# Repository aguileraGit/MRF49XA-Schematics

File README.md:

MRF49XA-Schematics
==================

MRF49XA Schematics and Layout

Project page for a wireless board. This board uses the MicroChip MRF49XA and Atmel ATMEGA32U4.

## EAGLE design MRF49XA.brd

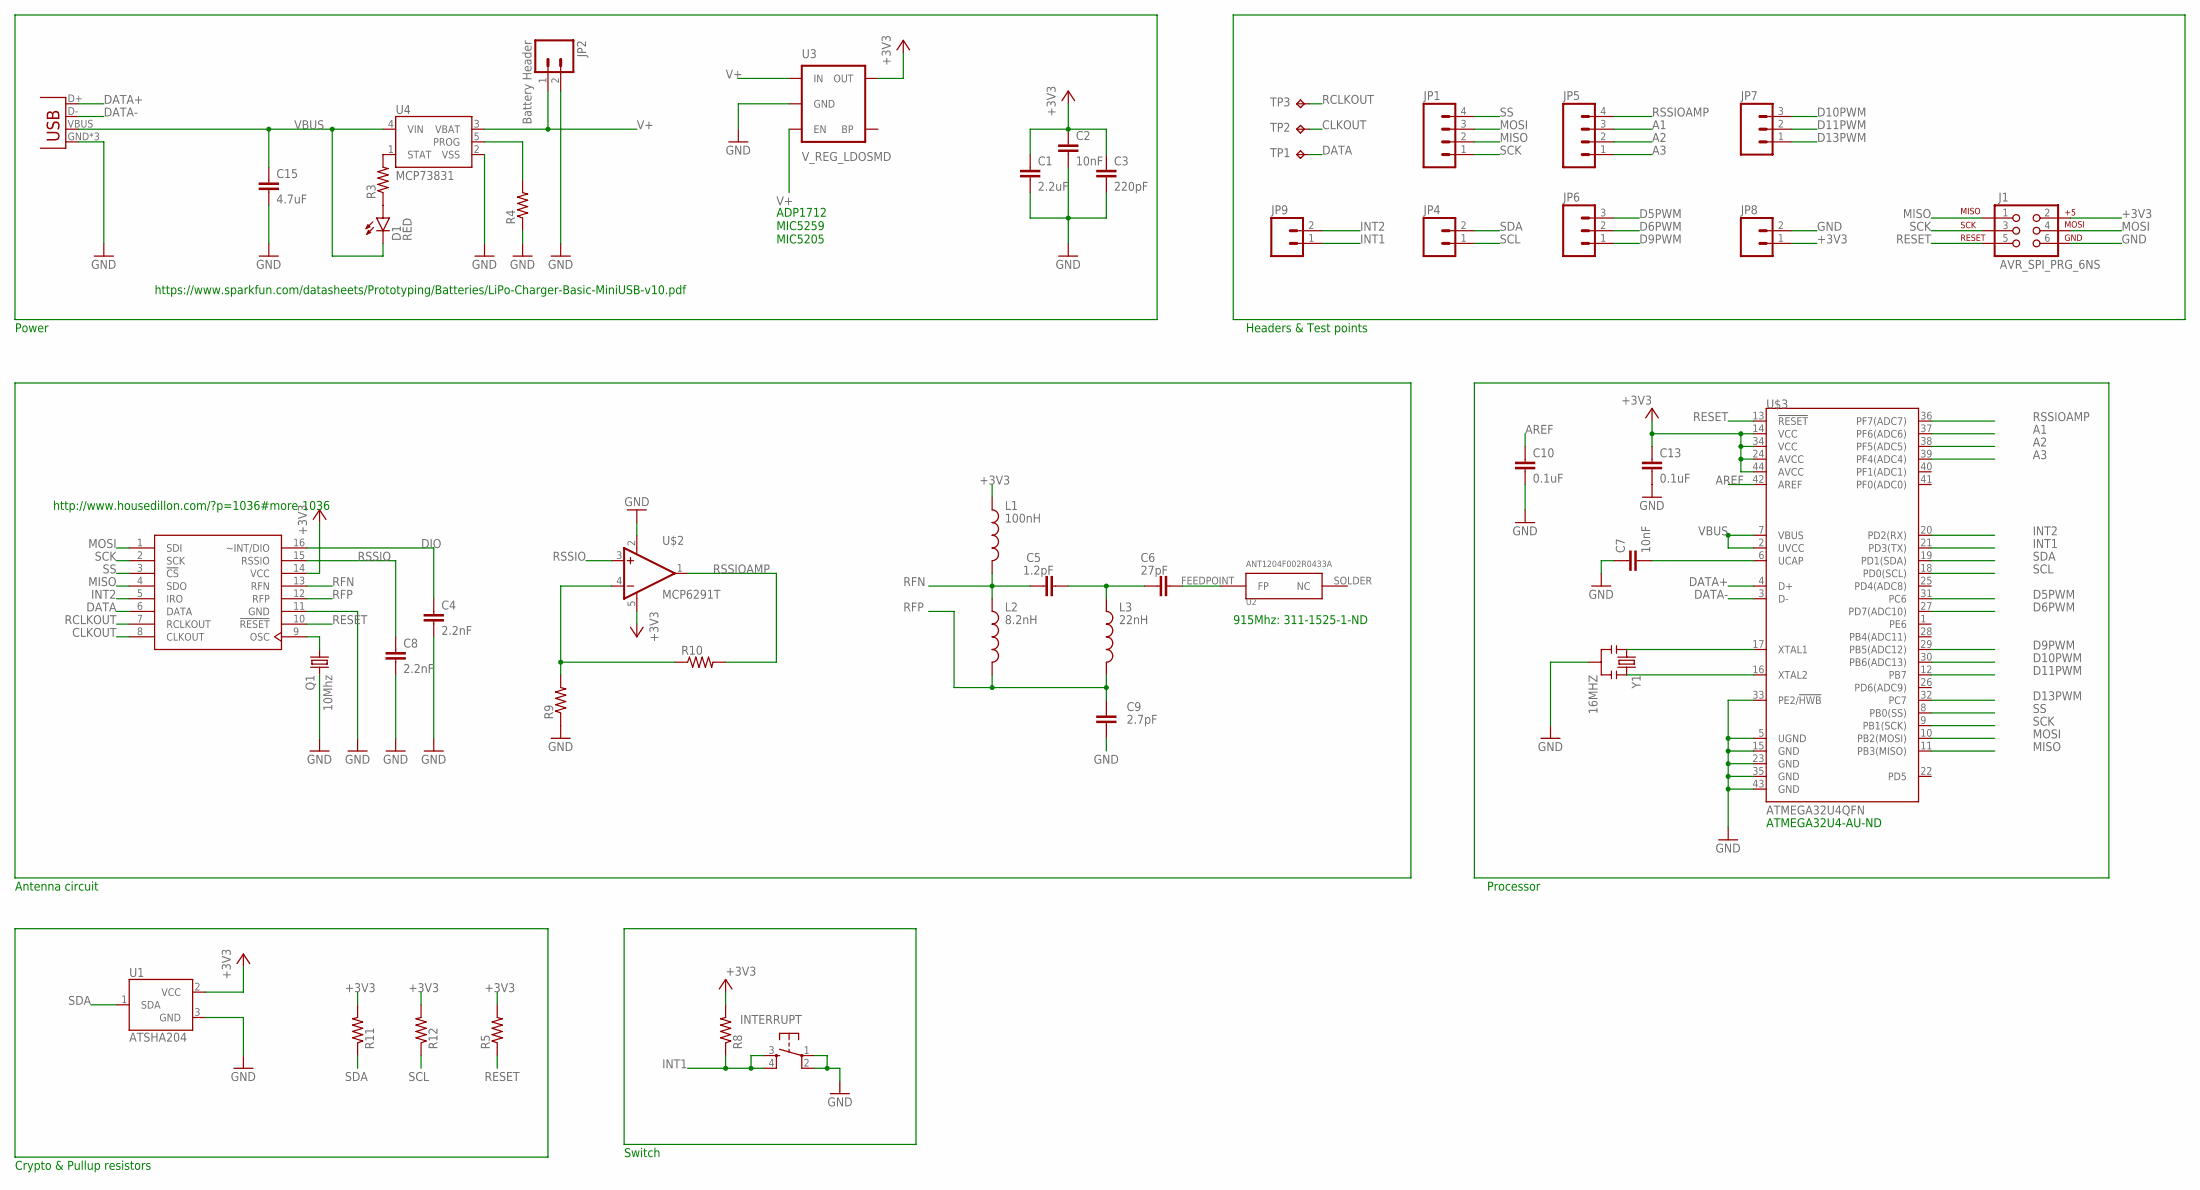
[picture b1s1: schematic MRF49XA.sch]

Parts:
C1: 2.2uF; 0603-CAP
C2, C7: 10nF; 0603-CAP
C3: 220pF; 0603-CAP
C4, C8: 2.2nF; 0603-CAP
C5: 1.2pF; 0603-CAP
C6: 27pF; 0603-CAP
C9: 2.7pF; 0603-CAP
C10, C13: 0.1uF; 0603-CAP
C15: 4.7uF; C3216
D1: RED; LED-0603
INTERRUPT: TAC_SWITCHSMD; TACTILE-SWITCH-SMD
J1: AVR_SPI_PRG_6NS; 2X3-NS
JP1, JP5: M04PTH; 1X04
JP2: Battery Header; 1X02_LOCK_LONGPADS
JP3: USB-MICROB
JP4, JP8, JP9: M02PTH; 1X02
JP6, JP7: M03PTH; 1X03
L1: 100nH; 0603
L2: 8.2nH; 0603
L3: 22nH; 0603
Q1: 10Mhz; CTS406
R3: RESISTOR0603-RES; 0603-RES
R4, R5, R8, R9, R10, R11, R12: R-US_R0603; R0603
TP1, TP2, TP3: TPTP08R; TP08R
U1: ATSHA204; SOT23-3
U2: ANT1204F002R0433A
U3: V_REG_LDOSMD; SOT23-5
U4: MCP73831; SOT23-5
U$1: MRF49XA; TSSOP16
U$2: MCP6291T; SOT23-5
U$3: ATMEGA32U4QFN; QFN-44
Y1: 16MHZ; RESONATOR-SMD

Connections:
+3V3: C1.1, C2.1, C3.1, C13.1, J1.2, JP8.1, L1.1, R5.2, R8.2, R11.2, R12.2, U1.2 (VCC), U3.5 (OUT), U$1.14 (VCC), U$2.5 (V+), U$3.14 (VCC), U$3.24 (AVCC), U$3.34 (VCC), U$3.44 (AVCC)
A1: JP5.3, U$3.37 (PF6(ADC6))
A2: JP5.2, U$3.38 (PF5(ADC5))
A3: JP5.1, U$3.39 (PF4(ADC4))
AREF: C10.1, U$3.42 (AREF)
CLKOUT: TP2.TP, U$1.8 (CLKOUT)
D5PWM: JP6.3, U$3.31 (PC6)
D6PWM: JP6.2, U$3.27 (PD7(ADC10))
D9PWM: JP6.1, U$3.29 (PB5(ADC12))
D10PWM: JP7.3, U$3.30 (PB6(ADC13))
D11PWM: JP7.2, U$3.12 (PB7)
D13PWM: JP7.1, U$3.32 (PC7)
DATA: TP1.TP, U$1.6 (DATA)
DATA+: JP3.D+, U$3.4 (D+)
DATA-: JP3.D-, U$3.3 (D-)
DIO: C4.1, U$1.16 (~INT/DIO)
GND: C1.2, C2.2, C3.2, C4.2, C7.1, C8.2, C9.2, C10.2, C13.2, C15.2, INTERRUPT.1, INTERRUPT.2, J1.6, JP2.2, JP3.GND, JP3.MT1 (GND), JP3.MT2 (GND), JP8.2, Q1.3 (2), R4.1, R9.1, U1.3 (GND), U3.2 (GND), U4.2 (VSS), U$1.11 (GND), U$2.2 (V-), U$3.5 (UGND), U$3.15 (GND), U$3.23 (GND), U$3.33 (PE2/!HWB), U$3.35 (GND), U$3.43 (GND), Y1.2
INT1: INTERRUPT.3, INTERRUPT.4, JP9.1, R8.1, U$3.21 (PD3(TX))
INT2: JP9.2, U$1.5 (IRO), U$3.20 (PD2(RX))
MISO: J1.1, JP1.2, U$1.4 (SDO), U$3.11 (PB3(MISO))
MOSI: J1.4, JP1.3, U$1.1 (SDI), U$3.10 (PB2(MOSI))
unnamed: Q1.1, U$1.9 (OSC)
unnamed: U$3.16 (XTAL2), Y1.3
unnamed: U$3.17 (XTAL1), Y1.1
unnamed: R3.2, U4.1 (STAT)
unnamed: D1.A, R3.1
unnamed: R4.2, U4.5 (PROG)
unnamed: C7.2, U$3.6 (UCAP)
unnamed: C5.2, C6.1, L3.1
unnamed: R9.2, R10.1, U$2.4 (-IN)
unnamed: C6.2, U2.FEEDPOINT (FP)
RCLKOUT: TP3.TP, U$1.7 (RCLKOUT)
RESET: J1.5, R5.1, U$1.10 (!RESET), U$3.13 (!RESET)
RFN: C5.1, L1.2, L2.1, U$1.13 (RFN)
RFP: C9.1, L2.2, L3.2, U$1.12 (RFP)
RSSIO: C8.1, U$1.15 (RSSIO), U$2.3 (+IN)
RSSIOAMP: JP5.4, R10.2, U$2.1 (OUT), U$3.36 (PF7(ADC7))
SCK: J1.3, JP1.1, U$1.2 (SCK), U$3.9 (PB1(SCK))
SCL: JP4.1, R12.1, U$3.18 (PD0(SCL))
SDA: JP4.2, R11.1, U1.1 (SDA), U$3.19 (PD1(SDA))
SS: JP1.4, U$1.3 (!CS), U$3.8 (PB0(SS))
V+: JP2.1, U3.1 (IN), U3.3 (EN), U4.3 (VBAT)
VBUS: C15.1, D1.C, JP3.VBUS, U4.4 (VIN), U$3.2 (UVCC), U$3.7 (VBUS)
VSS: U$1.P$1 (VSS)

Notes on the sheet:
https://www.sparkfun.com/datasheets/Prototyping/Batteries/LiPo-Charger-Basic-MiniUSB-v10.pdf
http://www.housedillon.com/?p=1036#more-1036
ATMEGA32U4-AU-ND
915Mhz: 311-1525-1-ND
Power
Antenna circuit
Crypto & Pullup resistors
Switch
Processor
Headers & Test points
ADP1712 MIC5259 MIC5205

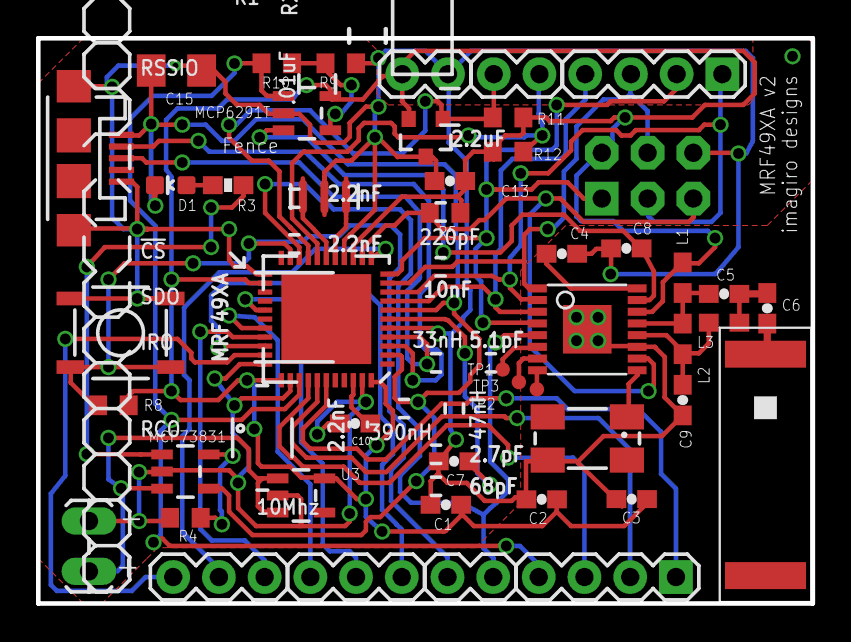
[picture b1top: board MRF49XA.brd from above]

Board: 2 copper layers, 43.0 x 31.4 mm, 47 parts (0 on the bottom side), 43 nets.

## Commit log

2014-12-09 MRF49XA Schematics
    Contains schematics and layout.
2014-12-11 PDF
    Added PDF of the circuit.
2014-12-12 Linear regulator changed
    Changed it. Cheaper. Plus the other one would have blown up my circuit.
2014-12-16 Capacitor and V reg
    Added Aref capacitor. Changed voltage regulator.
2014-12-18 Updates & PDF
    More updates and PDF
2014-12-19 V Regulators
    Added a list of possible voltage regulators.
2014-12-31 BOM
    Added BOM and values to antenna section
2014-12-31 Created README.md
2015-01-09 Adding bootloader
2015-01-13 Code
    Adding code
2015-01-13 Code update
2015-01-14 CS
    Updated the CS pin.
    Adding SPI debug file
2015-01-14 Code update
    Added sendPacket
2015-01-15 Code update
    Reading for status register is constantly changing.
2015-01-16 Update schematics
2015-01-16 Adding Jpeg of schematics
2015-01-16 Added layout pdf
2015-01-22 More code testing
    Still seeing “random” values.
2015-01-27 Added demo port
    Demo code sent from Microchip that I’m porting over to Arduino.
2015-01-28 Updated code - Still see same error as before

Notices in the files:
MRF49XA.brd:
(C) 2010 - William Dillon KD7VMY
Licensed under the
TAPR Open Hardware License
parts and their libraries:
SparkFun-DigitalIC: Licensing: Creative Commons ShareAlike 4.0 International - https://creativecommons.org/licenses/by-sa/4.0
